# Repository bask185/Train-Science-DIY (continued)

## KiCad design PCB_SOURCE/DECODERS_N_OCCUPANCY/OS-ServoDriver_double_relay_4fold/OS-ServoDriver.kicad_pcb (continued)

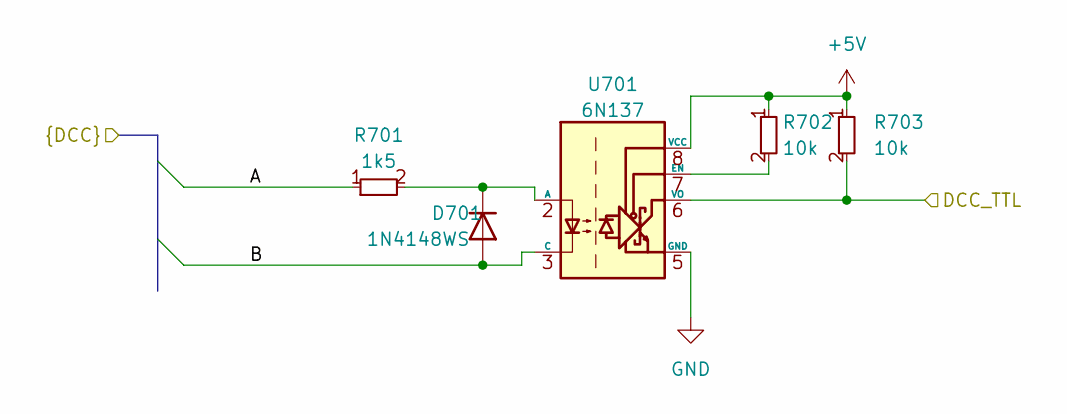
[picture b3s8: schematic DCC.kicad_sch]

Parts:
D701: 1N4148WS; D_SOD-323; JLCPCB Part# C2128
R701: 1k5; R_0603_smalltext; JLCPCB Part# C22843
R702, R703: 10k; R_0603_smalltext; JLCPCB Part# C25804
U701: 6N137; SOP-8_6.62x9.15mm_P2.54mm; JLCPCB Part# C110020

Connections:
/DCC/DCC_TTL: R703.2, U701.6 (VO); also elsewhere on the board
/DCC_A: R701.1; also elsewhere on the board
/DCC_B: D701.2 (A), U701.3 (C); also elsewhere on the board
unnamed: D701.1 (K), R701.2, U701.2 (A)
unnamed: R702.2, U701.7 (EN)

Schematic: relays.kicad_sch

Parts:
D801, D802: 1N4148WS; D_SOD-323; JLCPCB Part# C2128
K801, K802: G6K-2F-Y-TR DC5; Relay_DPDT_Omron_G6K-2F-Y; JLCPCB Part# C47190
Q801, Q802: AO3400A; SOT-23; JLCPCB Part# C20917
R801, R802: 22R; R_0603_smalltext; JLCPCB Part# C23345
R803, R804: 10k; R_0603_smalltext; JLCPCB Part# C25804

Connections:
+5VA: D801.1 (K), D802.1 (K), K801.1, K802.1; also elsewhere on the board
/DCC_A: K801.4; also elsewhere on the board
/DCC_B: K802.4; also elsewhere on the board
/Servo1-2/Frog1: K801.3, K802.3; also elsewhere on the board
/Servo1-2/Relay1: R801.1; also elsewhere on the board
/Servo1-2/Relay2: R802.1; also elsewhere on the board
unnamed: D801.2 (A), K801.8, Q801.3 (D)
unnamed: D802.2 (A), K802.8, Q802.3 (D)
unnamed: Q801.1 (G), R801.2, R803.2
unnamed: Q802.1 (G), R802.2, R804.2

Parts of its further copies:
D901, D902, D1001, D1002, D1101, D1102: 1N4148WS; D_SOD-323; JLCPCB Part# C2128
K901, K902, K1001, K1002, K1101, K1102: G6K-2F-Y-TR DC5; Relay_DPDT_Omron_G6K-2F-Y; JLCPCB Part# C47190
Q901, Q902, Q1001, Q1002, Q1101, Q1102: AO3400A; SOT-23; JLCPCB Part# C20917
R904, R905, R1001, R1002, R1101, R1102: 22R; R_0603_smalltext; JLCPCB Part# C23345
R906, R907, R1003, R1004, R1103, R1104: 10k; R_0603_smalltext; JLCPCB Part# C25804

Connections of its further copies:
+5VA: D901.1 (K), D902.1 (K), D1001.1 (K), D1002.1 (K), D1101.1 (K), D1102.1 (K), K901.1, K902.1, K1001.1, K1002.1, K1101.1, K1102.1; also elsewhere on the board
/DCC_A: K901.4, K1001.4, K1101.4; also elsewhere on the board
/DCC_B: K902.4, K1002.4, K1102.4; also elsewhere on the board
/Servo1-2/Frog2: K901.3, K902.3; also elsewhere on the board
/Servo1-2/Relay3: R904.1; also elsewhere on the board
/Servo1-2/Relay4: R905.1; also elsewhere on the board
/Servo3-4/Frog1: K1101.3, K1102.3; also elsewhere on the board
/Servo3-4/Frog2: K1001.3, K1002.3; also elsewhere on the board
/Servo3-4/Relay1: R1101.1; also elsewhere on the board
/Servo3-4/Relay2: R1102.1; also elsewhere on the board
/Servo3-4/Relay3: R1001.1; also elsewhere on the board
/Servo3-4/Relay4: R1002.1; also elsewhere on the board
unnamed: D901.2 (A), K901.8, Q901.3 (D)
unnamed: D902.2 (A), K902.8, Q902.3 (D)
unnamed: D1001.2 (A), K1001.8, Q1001.3 (D)
unnamed: D1002.2 (A), K1002.8, Q1002.3 (D)
unnamed: D1101.2 (A), K1101.8, Q1101.3 (D)
unnamed: D1102.2 (A), K1102.8, Q1102.3 (D)
unnamed: Q901.1 (G), R904.2, R906.2
unnamed: Q902.1 (G), R905.2, R907.2
unnamed: Q1001.1 (G), R1001.2, R1003.2
unnamed: Q1002.1 (G), R1002.2, R1004.2
unnamed: Q1101.1 (G), R1101.2, R1103.2
unnamed: Q1102.1 (G), R1102.2, R1104.2

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
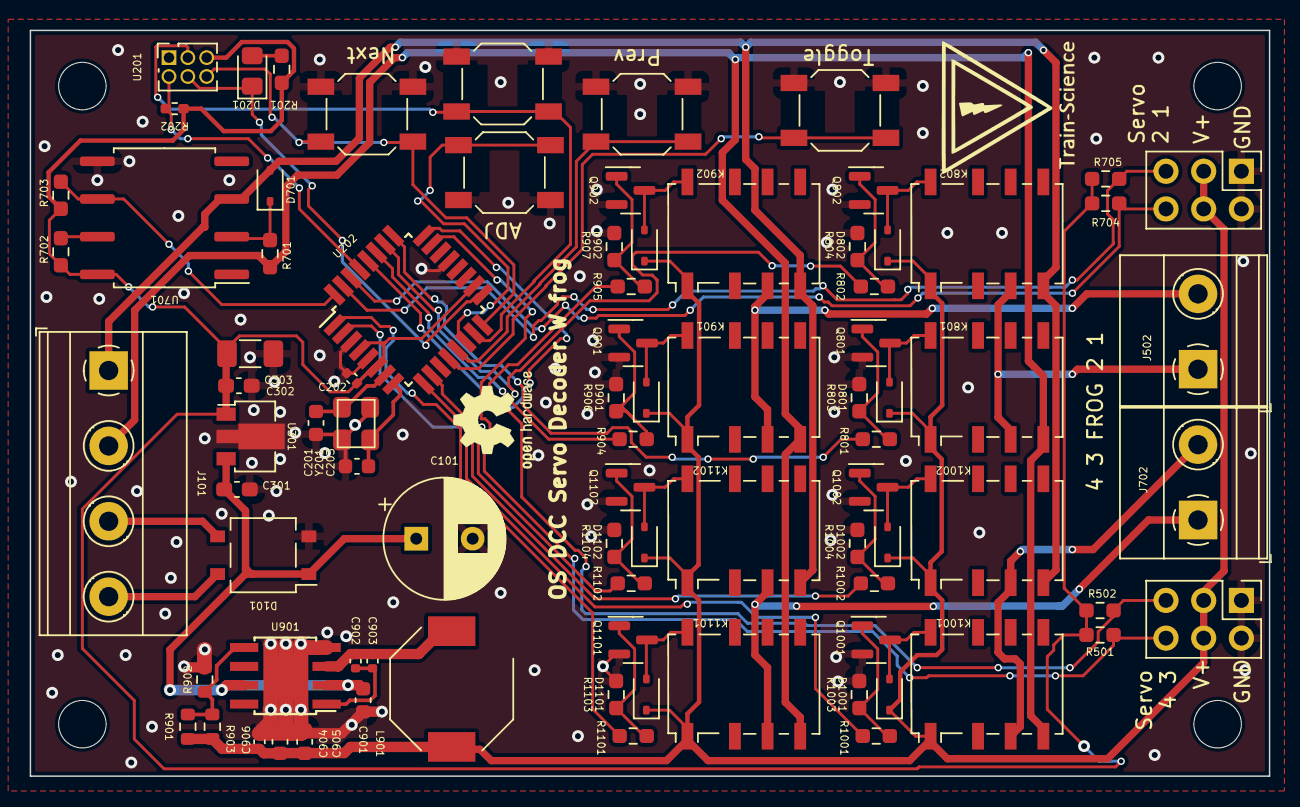
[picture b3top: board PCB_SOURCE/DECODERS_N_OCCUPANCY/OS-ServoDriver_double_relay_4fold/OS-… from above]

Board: 2 copper layers, 83.5 x 50.2 mm, 85 parts (0 on the bottom side), 56 nets.

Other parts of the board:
C101: 100uF; CP_Radial_D8.0mm_P3.80mm

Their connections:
VCC: C101.1; also elsewhere on the board

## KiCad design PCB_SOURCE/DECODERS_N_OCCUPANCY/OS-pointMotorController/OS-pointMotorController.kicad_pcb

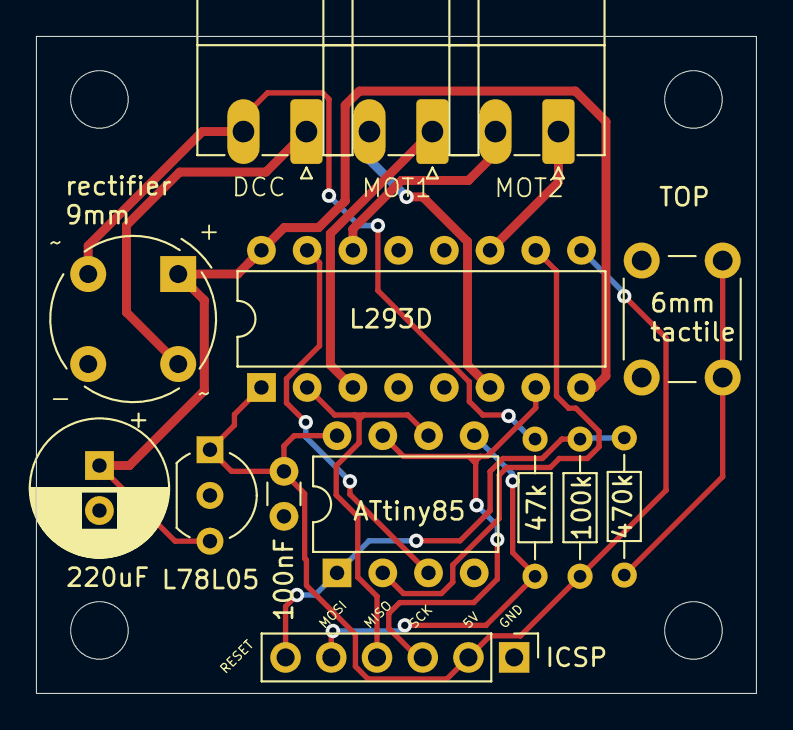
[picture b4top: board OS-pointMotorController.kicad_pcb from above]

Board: 2 copper layers, 40.0 x 36.5 mm, 14 parts (0 on the bottom side), 16 nets.

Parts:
C2: 220uF; CP_Radial_D7.5mm_P2.50mm
C3: 100nF; C_Disc_D3.0mm_W1.6mm_P2.50mm
D1: D_Bridge_+A-A; Diode_Bridge_Round_D9.0mm
J1, J2, J3: Screw_Terminal_01x02; PhoenixContact_MC_1,5_2-G-3.5_1x02_P3.50mm_Horizontal
J4: ICSP; PinHeader_1x06_P2.54mm_Vertical
R1: 47k; R_Axial_DIN0204_L3.6mm_D1.6mm_P7.62mm_Horizontal
R2: 100k; R_Axial_DIN0204_L3.6mm_D1.6mm_P7.62mm_Horizontal
R3: 470k; R_Axial_DIN0204_L3.6mm_D1.6mm_P7.62mm_Horizontal
SW1: 6mm_tactile; SW_NO_SILK
U1: L293D; DIP-16_W7.62mm
U2: L78L05; TO-92_Inline_Wide
U3: ATtiny85; DIP-8_W7.62mm

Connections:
+5V: C3.1, J4.2, R2.1, U1.1 (EN1,2), U1.9 (EN3,4), U2.1 (VO), U3.8 (VCC)
/1A: J4.4, U1.2 (1A), U3.6 (PB1)
/1B: J4.3, U1.7 (2A), U3.7 (PB2)
/2A: U1.10 (3A), U3.2 (XTAL1/PB3)
/2B: U1.15 (4A), U3.3 (XTAL2/PB4)
/DCC_A: D1.4, J1.1
/DCC_B: D1.2, J1.2, R1.2
/MOSI: J4.5, R1.1, U3.5 (AREF/PB0)
/RESET: J4.6, R2.2, R3.1, U3.1 (~RESET/PB5)
GND: C2.2, C3.2, D1.3 (-), J4.1, SW1.1 (A), U1.4 (GND), U1.5 (GND), U1.12 (GND), U1.13 (GND), U2.2 (GND), U3.4 (GND)
unnamed: J2.1, U1.3 (1Y)
unnamed: J2.2, U1.6 (2Y)
unnamed: J3.1, U1.11 (3Y)
unnamed: J3.2, U1.14 (4Y)
unnamed: R3.2, SW1.2 (B)
VCC: C2.1, D1.1 (+), U1.8 (VCC2), U1.16 (VCC1), U2.3 (VI)

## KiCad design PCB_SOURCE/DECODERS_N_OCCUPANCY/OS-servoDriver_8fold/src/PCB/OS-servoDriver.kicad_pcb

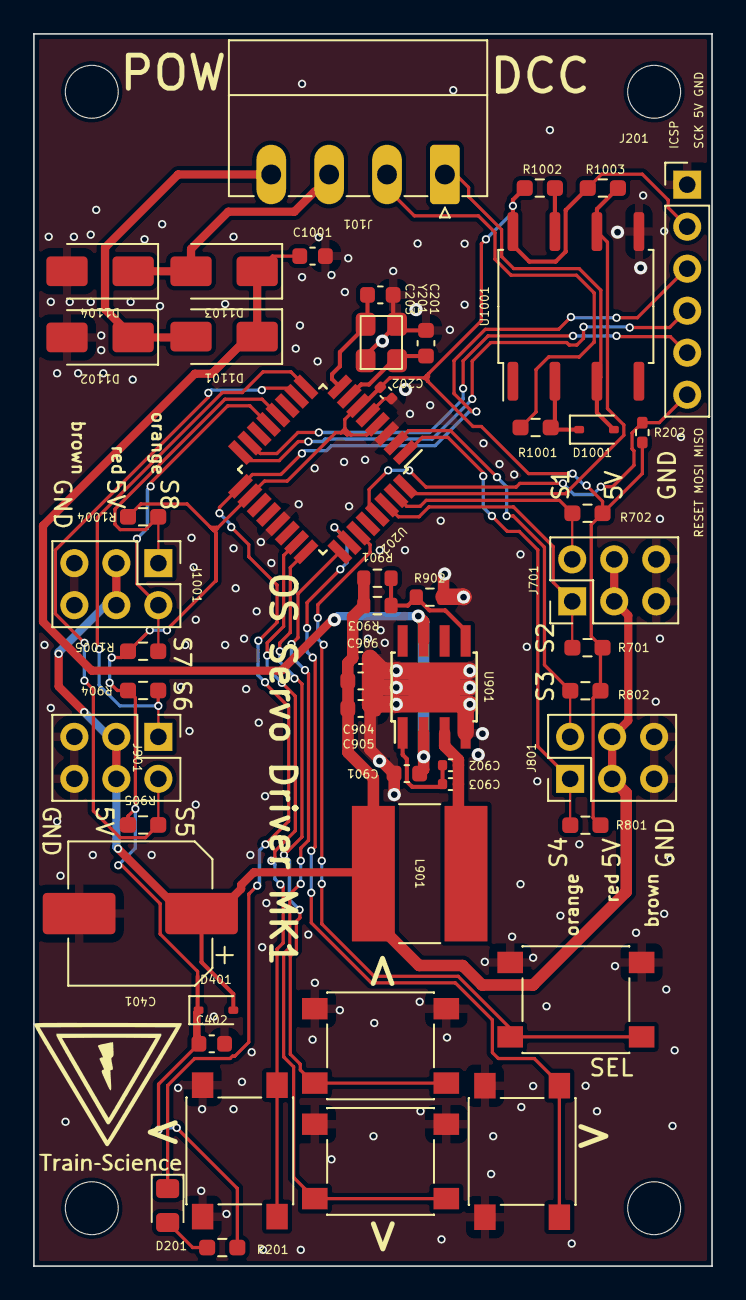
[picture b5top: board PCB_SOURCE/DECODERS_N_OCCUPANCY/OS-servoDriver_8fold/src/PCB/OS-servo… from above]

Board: 2 copper layers, 41.0 x 74.5 mm, 51 parts (0 on the bottom side), 34 nets.

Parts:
C201, C203: 12pF; C_0603_1608Metric
C202, C902, C906: 100nF; C_0402_1005Metric
C401: 1000uF; CP_Elec_8x10.5
C402, C901, C904, C905: 22uF; C_0603_1608Metric
C903: 22nF; C_0402_1005Metric
C1001: 100nF; C_0603_1608Metric
D201: LED; LED_0805_2012Metric_Pad1.15x1.40mm_HandSolder
D401, D1001: 1N4148WS; D_SOD-323
D1101, D1102, D1103, D1104: SS53; D_SMA
J101: Screw_Terminal_01x04; PhoenixContact_MC_1,5_4-G-3.5_1x04_P3.50mm_Horizontal
J201: ICSP; PinHeader_1x06_P2.54mm_Vertical
J701, J801, J901, J1001: Conn_02x03_Odd_Even; PinHeader_2x03_P2.54mm_Vertical
L901: L; L_Bourns-SRN8040_8x8.15mm
R201: 6k2; R_0603_1608Metric_Pad0.98x0.95mm_HandSolder
R202: 10k; R_0402_1005Metric_Pad0.72x0.64mm_HandSolder
R701, R702, R801, R802, R904, R905, R1002, R1003, R1004, R1005: 10k; R_0603_smalltext
R901: 220k; R_0603_1608Metric
R902: 20k; R_0603_1608Metric
R903: 150k; R_0603_1608Metric
R1001: 1k; R_0603_smalltext
SW601, SW602, SW603, SW604, SW605: SW_Push; tactile_SMD_6mm
U202: ATmega328-A; TQFP-32_7x7mm_P0.8mm
U901: MT2499A; TI_SO-PowerPAD-8
U1001: 6N137; SOP-8_6.62x9.15mm_P2.54mm
Y201: Crystal_GND2; crystal_arduino

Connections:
+5V: C202.1, C402.1, D401.1 (K), J201.2, R201.1, R202.2, R701.2, R702.2, R801.2, R802.2, R904.2, R905.2, R1002.1, R1003.1, R1004.2, R1005.2, U202.4 (VCC), U202.6 (VCC), U202.18 (AVCC), U1001.8 (VCC)
+5VA: C401.1, C904.1, C905.1, C906.1, D401.2 (A), J701.3, J701.4, J801.3, J801.4, J901.3, J901.4, J1001.3, J1001.4, L901.2, R901.1, R903.2
/DCC/DCC_A: J101.2, R1001.1
/DCC/DCC_B: D1001.2 (A), J101.1, U1001.3 (C)
/DCC/DCC_TTL: R1003.2, U202.32 (PD2), U1001.6 (VO)
/D_bridge/AC_1: D1101.2 (A), D1102.1 (K), J101.4
/D_bridge/AC_2: D1103.2 (A), D1104.1 (K), J101.3
/atmega/LED: D201.1 (K), J201.3, U202.17 (PB5)
/atmega/MISO: J201.4, U202.16 (PB4)
/atmega/MOSI: J201.5, U202.15 (PB3)
/atmega/X1: C201.2, U202.7 (XTAL1/PB6), Y201.1
/atmega/X2: C203.2, U202.8 (XTAL2/PB7), Y201.3
/atmega/bus1.pin1: J701.1, R701.1, U202.30 (PD0)
/atmega/bus1.pin2: J701.2, R702.1, U202.31 (PD1)
/atmega/bus2.pin1: J801.1, R801.1, U202.1 (PD3)
/atmega/bus2.pin2: J801.2, R802.1, U202.2 (PD4)
/atmega/bus3.pin1: J901.1, R904.1, U202.9 (PD5)
/atmega/bus3.pin2: J901.2, R905.1, U202.10 (PD6)
/atmega/bus4.pin1: J1001.1, R1004.1, U202.12 (PB0)
/atmega/bus4.pin2: J1001.2, R1005.1, U202.13 (PB1)
/atmega/reset: J201.6, R202.1, U202.29 (~RESET/PC6)
/atmega/sw1: SW601.2, U202.23 (PC0)
/atmega/sw2: SW602.2, U202.24 (PC1)
/atmega/sw3: SW603.2, U202.25 (PC2)
/atmega/sw4: SW604.2, U202.26 (PC3)
/atmega/sw5: SW605.2, U202.27 (PC4)
GND: C201.1, C202.2, C203.1, C401.2, C402.2, C901.2, C904.2, C905.2, C906.2, C1001.2, D1102.2 (A), D1104.2 (A), J201.1, J701.5, J701.6, J801.5, J801.6, J901.5, J901.6, J1001.5, J1001.6, R902.2, SW601.1, SW602.1, SW603.1, SW604.1, SW605.1, U202.3 (GND), U202.5 (GND), U202.21 (GND), U901.4 (GND), U901.9 (GND), U1001.5 (GND), Y201.2 (GND), Y201.4 (GND)
unnamed: D201.2 (A), R201.2
unnamed: D1001.1 (K), R1001.2, U1001.2 (A)
unnamed: C902.1, C903.1, U901.1 (BS)
unnamed: R901.2, R902.1, R903.1, U901.5 (FB)
unnamed: C902.2, C903.2, L901.1, U901.3 (SW)
unnamed: R1002.2, U1001.7 (EN)
VCC: C901.1, C1001.1, D1101.1 (K), D1103.1 (K), U901.2 (Vin), U901.7 (EN)
